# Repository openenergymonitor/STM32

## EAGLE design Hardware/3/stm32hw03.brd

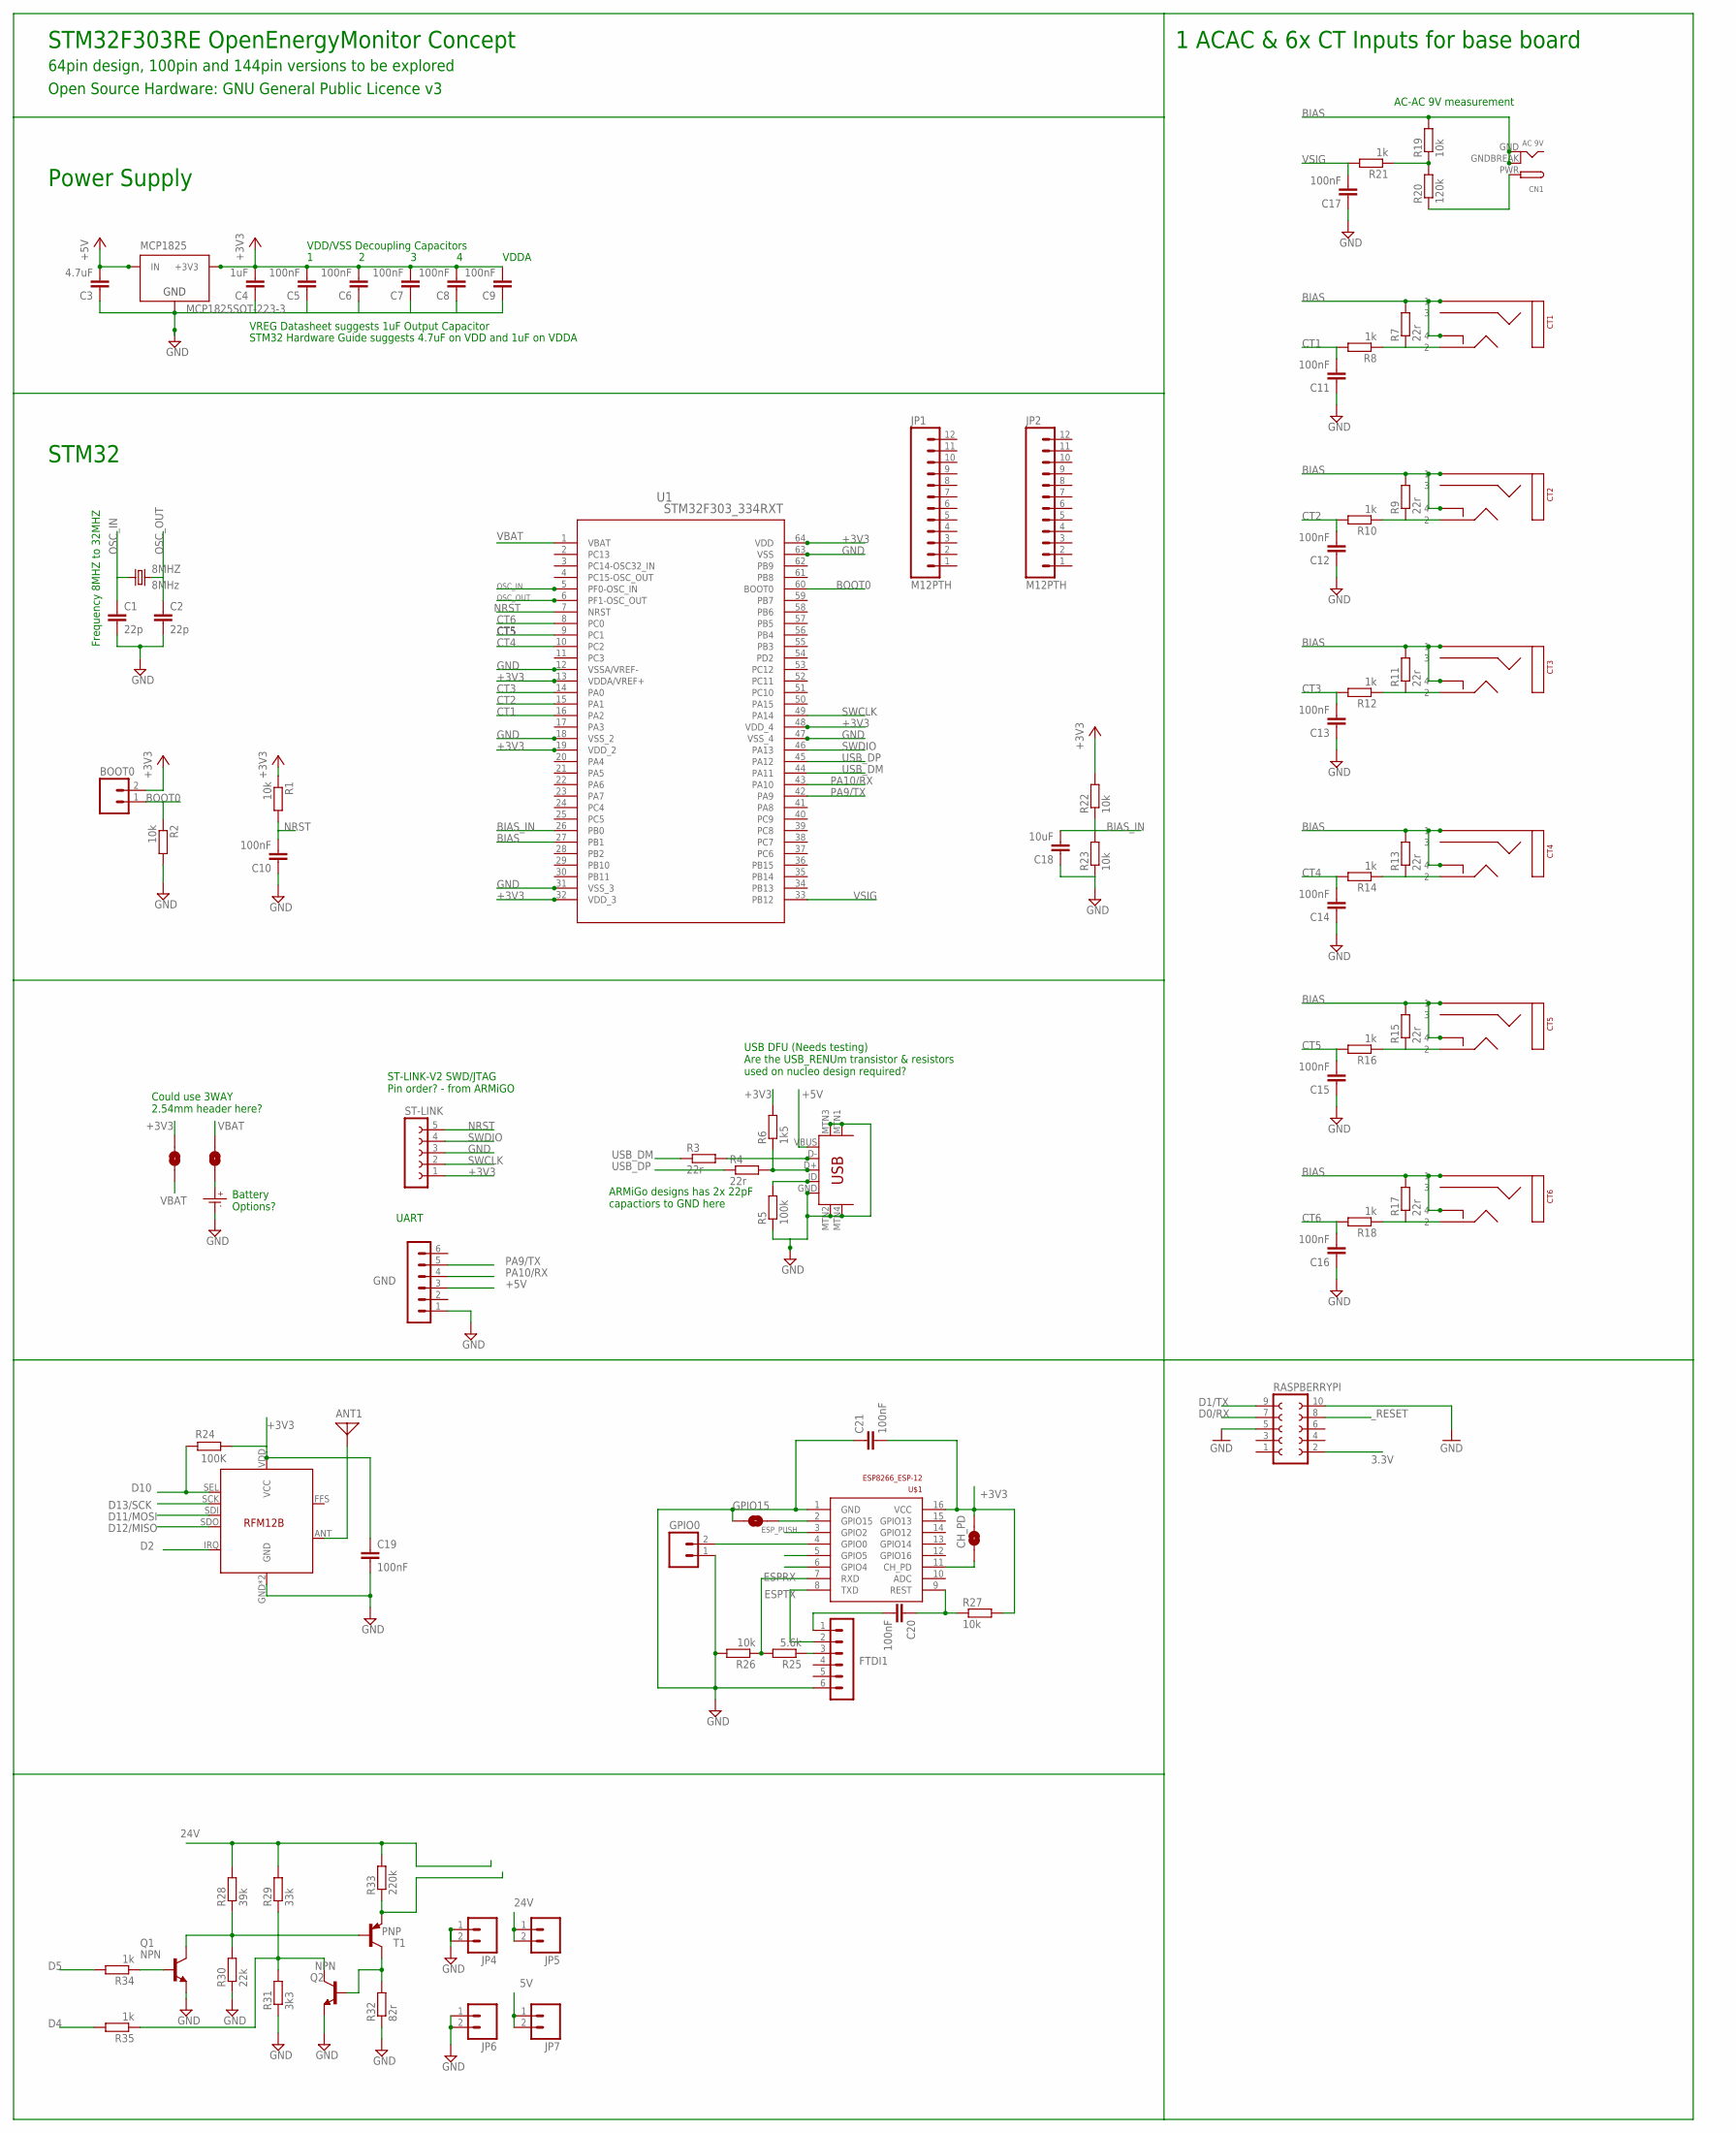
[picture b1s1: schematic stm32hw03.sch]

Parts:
3V3: SOLDERJUMPERNO; SJ_2S-NO
8MHZ: 8MHz; CRYSTAL-SMD-5X3
ANT1: ANTENNA; PAD-01
BATTERY: SOLDERJUMPERNO; SJ_2S-NO
BOOT0: M02PTH; 1X02
C1, C2: 22p; C0603
C3: 4.7uF; C0603
C4: 1uF; C0603
C5, C6, C7, C8, C9, C10, C11, C12, C13, C14, C15, C16, C17, C19, C20, C21: 100nF; C0603
C18: 10uF; C0603
CH_PD: SOLDERJUMPERNO; SJ_2S-NO
CN1: AC 9V; DCJACK_2MM_PTH
CR1220: CR1220SMD; MPN Harwin S8411-45R
CT1, CT2, CT3, CT4, CT5, CT6: STEREO_SMD; STEREO_SMT
FTDI1: FTDI; MA06-1
GND: UART; MA06-1
GPIO0: M02PTH; 1X02
GPIO15: SOLDERJUMPERNO; SJ_2S-NO
JP1, JP2: M12PTH; 1X12
JP4, JP5, JP6, JP7: M02PTH; 1X02
MCP1825: MCP1825SOT-223-3; SOT-223
Q1, Q2: NPN; SOT23-BEC
R1, R2, R19, R22, R23, R26, R27: 10k; R0603
R3, R4, R7, R9, R11, R13, R15, R17: 22r; R0603
R5: 100k; R0603
R6: 1k5; R0603
R8, R10, R12, R14, R16, R18, R21, R34, R35: 1k; R0603
R20: 120k; R0603
R24: 100K; R0603
R25: 5.6k; R0603
R28: 39k; R0603
R29: 33k; R0603
R30: 22k; R0603
R31: 3k3; R0603
R32: 82r; R0603
R33: 220k; R0603
RASPBERRYPI: FE05-2
ST-LINK: FE05-1
T1: PNP; SOT23
U1: STM32F303_334RXT; LQFP64-10X10MM
U$1: ESP8266_ESP-12; ESP8266-ESP12
U$10: USB-MINIB-5PIN; USB-MINIB-CISECO
U$14: RFM12B

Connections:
3.3V: RASPBERRYPI.2
5V: JP7.1, JP7.2
24V: JP5.1, JP5.2, R28.2, R29.2, R33.2
+3V3: 3V3.1, BOOT0.2, C4.2, C5.2, C6.2, C7.2, C8.2, C9.2, C19.1, C21.2, CH_PD.1, MCP1825.3 (+3V3), R1.1, R6.2, R22.2, R24.1, R27.2, ST-LINK.1, U1.13 (VDDA/VREF+), U1.19 (VDD_2), U1.32 (VDD_3), U1.48 (VDD_4), U1.64 (VDD), U$1.16 (VCC), U$14.VDD (VCC); also elsewhere on the board
+5V: C3.2, GND.3, MCP1825.1 (IN), U$10.VBUS
AC: CN1.PWR, R20.1
ADC0: R19.1, R20.2, R21.1
BIAS: CN1.GND, CN1.GNDBREAK, CT1.P$1 (1), CT1.P$4 (4), CT2.P$1 (1), CT2.P$4 (4), CT3.P$1 (1), CT3.P$4 (4), CT4.P$1 (1), CT4.P$4 (4), CT5.P$1 (1), CT5.P$4 (4), CT6.P$1 (1), CT6.P$4 (4), R7.2, R9.2, R11.2, R13.2, R15.2, R17.2, R19.2, U1.27 (PB1)
BIAS_IN: C18.2, R22.1, R23.2, U1.26 (PB0)
BOOT0: BOOT0.1, R2.1, U1.60 (BOOT0)
CT1: C11.2, R8.2, U1.16 (PA2)
CT2: C12.2, R10.2, U1.15 (PA1)
CT3: C13.2, R12.2, U1.14 (PA0)
CT4: C14.2, R14.2, U1.10 (PC2)
CT5: C15.2, R16.2, U1.9 (PC1)
CT6: C16.2, R18.2, U1.8 (PC0)
D0/RX: RASPBERRYPI.7
D1/TX: RASPBERRYPI.9
D2: U$14.IRQ
D4: R35.2
D5: R34.2
D10: R24.2, U$14.SEL
D11/MOSI: U$14.SDI
D12/MISO: U$14.SDO
D13/SCK: U$14.SCK
DIG1: ANT1.1, U$14.ANT
ESPRX: R25.2, R26.1, U$1.7 (RXD)
ESPTX: FTDI1.2, U$1.8 (TXD)
ESP_PUSH: U$1.3 (GPIO2)
GND: C1.2, C2.2, C3.1, C4.1, C5.1, C6.1, C7.1, C8.1, C9.1, C10.1, C11.1, C12.1, C13.1, C14.1, C15.1, C16.1, C17.1, C18.1, C19.2, C21.1, CR1220.P- (P$-), FTDI1.6, GND.1, GPIO0.1, GPIO15.2, JP4.1, JP4.2, JP6.1, JP6.2, MCP1825.2 (GND), Q1.E, Q2.E, R2.2, R5.1, R23.1, R26.2, R30.1, R31.1, R32.1, RASPBERRYPI.5, RASPBERRYPI.10, ST-LINK.3, U1.12 (VSSA/VREF-), U1.18 (VSS_2), U1.31 (VSS_3), U1.47 (VSS_4), U1.63 (VSS), U$1.1 (GND), U$10.GND, U$10.MTN1 (MTN2), U$10.MTN2 (MTN3), U$10.MTN3 (MTN1), U$10.MTN4, U$14.GND, U$14.P$12 (GND); also elsewhere on the board
unnamed: BATTERY.2, CR1220.P+ (P$+)
unnamed: CT1.P$2 (2), R7.1, R8.1
unnamed: R5.2, U$10.ID
unnamed: R4.2, R6.1, U$10.D+
unnamed: R3.2, U$10.D-
unnamed: CT2.P$2 (2), R9.1, R10.1
unnamed: C20.2, FTDI1.1
unnamed: CT3.P$2 (2), R11.1, R12.1
unnamed: CT4.P$2 (2), R13.1, R14.1
unnamed: R33.1, T1.2 (E)
unnamed: CT5.P$2 (2), R15.1, R16.1
unnamed: Q2.B, R32.2, T1.3 (C)
unnamed: CT6.P$2 (2), R17.1, R18.1
unnamed: Q1.C, R28.1, R30.2, T1.1 (B)
unnamed: Q2.C, R29.1, R31.2, R35.1
unnamed: Q1.B, R34.1
unnamed: GPIO15.1, U$1.2 (GPIO15)
unnamed: GPIO0.2, U$1.4 (GPIO0)
unnamed: FTDI1.3, R25.1
unnamed: CH_PD.2, U$1.11 (CH_PD)
unnamed: C20.1, R27.1, U$1.9 (REST)
NRST: C10.2, R1.2, ST-LINK.5, U1.7 (NRST)
OSC_IN: 8MHZ.1, C1.1, U1.5 (PF0-OSC_IN)
OSC_OUT: 8MHZ.3 (2), C2.1, U1.6 (PF1-OSC_OUT)
PA9/TX: GND.5, U1.42 (PA9)
PA10/RX: GND.4, U1.43 (PA10)
SWCLK: ST-LINK.2, U1.49 (PA14)
SWDIO: ST-LINK.4, U1.46 (PA13)
USB_DM: R3.1, U1.44 (PA11)
USB_DP: R4.1, U1.45 (PA12)
VBAT: 3V3.2, BATTERY.1, U1.1 (VBAT)
VSIG: C17.2, R21.2, U1.33 (PB12)
_RESET: RASPBERRYPI.8

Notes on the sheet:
VDD/VSS Decoupling Capacitors
VDDA
VREG Datasheet suggests 1uF Output Capacitor
STM32 Hardware Guide suggests 4.7uF on VDD and 1uF on VDDA
Frequency 8MHZ to 32MHZ
Could use 3WAY 2.54mm header here?
Battery Options?
ST-LINK-V2 SWD/JTAG Pin order? - from ARMiGO
UART
USB DFU (Needs testing) Are the USB_RENUm transistor & resistors used on nucleo design required?
ARMiGo designs has 2x 22pF capactiors to GND here
AC-AC 9V measurement
1 ACAC & 6x CT Inputs for base board
STM32F303RE OpenEnergyMonitor Concept
64pin design, 100pin and 144pin versions to be explored
Power Supply
STM32
Open Source Hardware: GNU General Public Licence v3

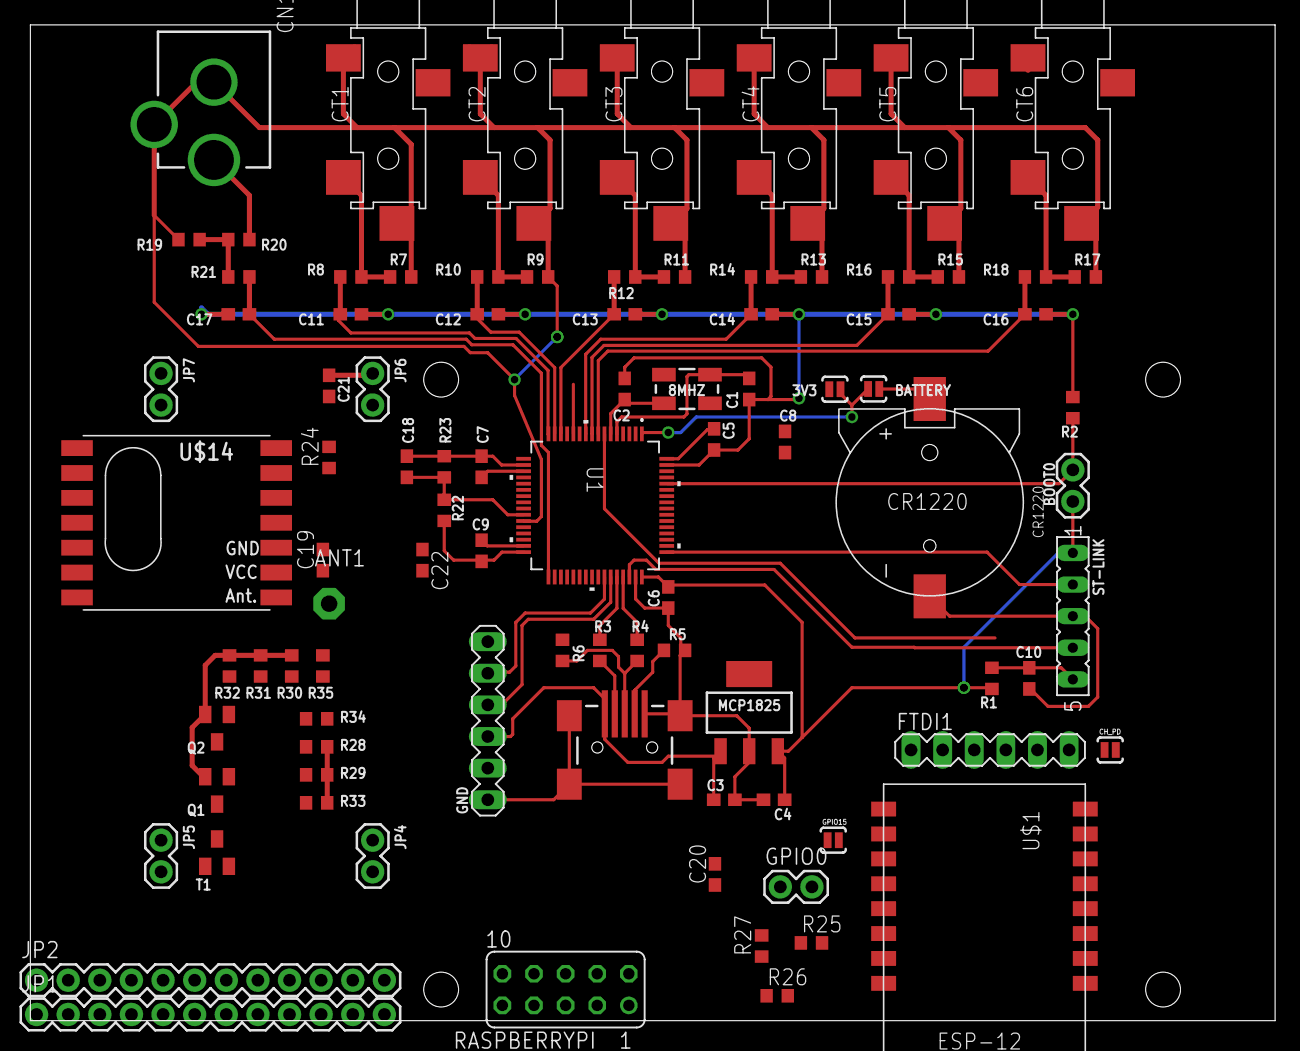
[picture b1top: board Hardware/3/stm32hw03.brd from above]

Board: 2 copper layers, 100.0 x 80.0 mm, 91 parts (0 on the bottom side), 52 nets.

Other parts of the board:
C22: 1uF; C0603

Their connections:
+3V3: C22.2; also elsewhere on the board
GND: C22.1; also elsewhere on the board

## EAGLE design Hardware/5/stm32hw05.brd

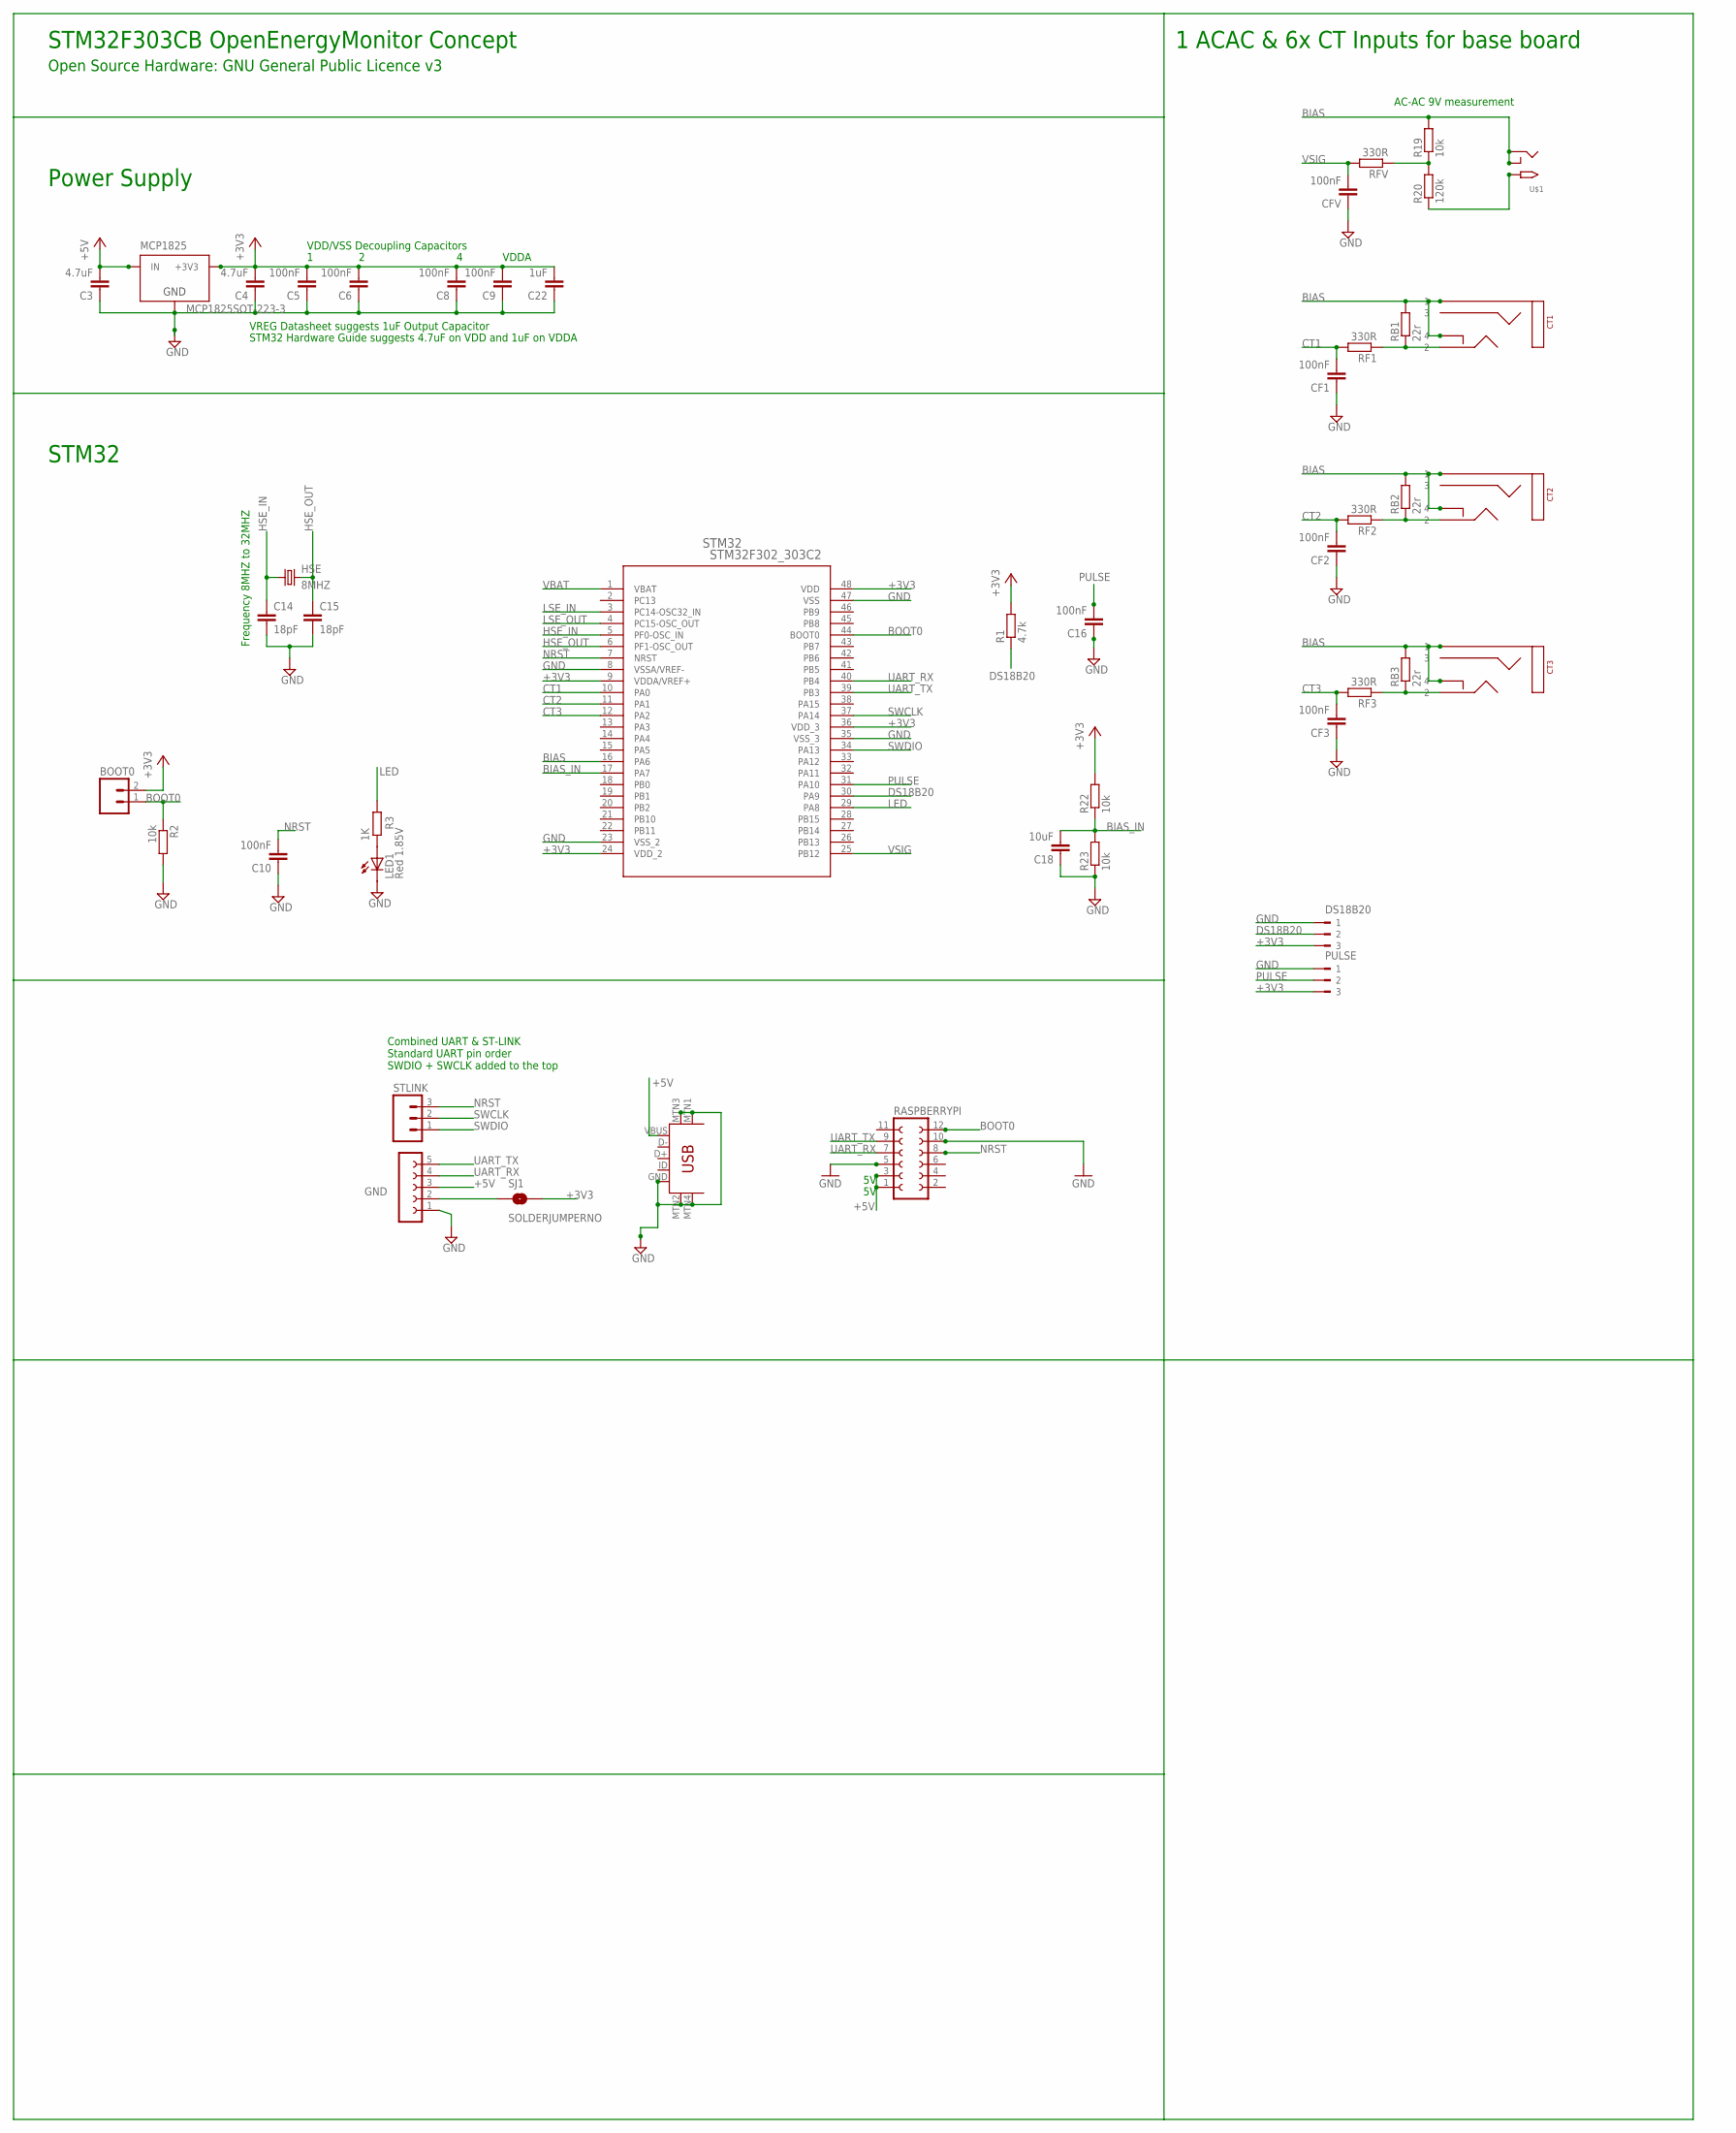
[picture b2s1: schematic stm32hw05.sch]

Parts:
BOOT0: M02PTH; 1X02
C3, C4: 4.7uF; C0603
C5, C6, C8, C9, C10, C16: 100nF; C0603
C14, C15: 18pF; C0603
C18: 10uF; C0603
C22: 1uF; C0603
CF1, CF2, CF3: 100nF; C0603
CFV: 100nF; C0603
CT1, CT2, CT3: STEREO_SMD; STEREO_SMT
DS18B20: 180-3
GND: UART; FE05-1
HSE: 8MHZ; CTS406
LED1: Red 1.85V; CHIP-LED0805
MCP1825: MCP1825SOT-223-3; SOT-223
PULSE: 180-3
R1: 4.7k; R0603
R2, R19, R22, R23: 10k; R0603
R3: 1K; R0603
R20: 120k; R0603
RASPBERRYPI: FE06-2
RB1, RB2, RB3: 22r; R0603
RF1, RF2, RF3: 330R; R0603
RFV: 330R; R0603
SJ1: SOLDERJUMPERNO; SJ_2S-NO
STLINK: M03PTH; 1X03
STM32: STM32F302_303C2; LQFP48-7X7MM
U$1: 2.1MMJACKSMT; DCJACK_2MM_SMT
U$10: USB-MINIB-5PIN; USB-MINIB-CISECO

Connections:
+3V3: BOOT0.2, C4.2, C5.2, C6.2, C8.2, C9.2, C22.2, DS18B20.3, MCP1825.3 (+3V3), PULSE.3, R1.2, R22.2, SJ1.2, STM32.9 (VDDA/VREF+), STM32.24 (VDD_2), STM32.36 (VDD_3), STM32.48 (VDD)
+5V: C3.2, GND.3, MCP1825.1 (IN), RASPBERRYPI.1, RASPBERRYPI.3, U$10.VBUS
AC: R20.1, U$1.PWR2 (TIP)
ADC0: R19.1, R20.2, RFV.1
BIAS: CT1.P$1 (1), CT1.P$4 (4), CT2.P$1 (1), CT2.P$4 (4), CT3.P$1 (1), CT3.P$4 (4), R19.2, RB1.2, RB2.2, RB3.2, STM32.16 (PA6), U$1.GND (RING), U$1.GNDBREAK (RING_SW)
BIAS_IN: C18.2, R22.1, R23.2, STM32.17 (PA7)
BOOT0: BOOT0.1, R2.1, RASPBERRYPI.12, STM32.44 (BOOT0)
CT1: CF1.2, RF1.2, STM32.10 (PA0)
CT2: CF2.2, RF2.2, STM32.11 (PA1)
CT3: CF3.2, RF3.2, STM32.12 (PA2)
DS18B20: DS18B20.2, R1.1, STM32.30 (PA9)
GND: C3.1, C4.1, C5.1, C6.1, C8.1, C9.1, C10.1, C14.2, C15.2, C16.1, C18.1, C22.1, CF1.1, CF2.1, CF3.1, CFV.1, DS18B20.1, GND.1, LED1.C, MCP1825.2 (GND), PULSE.1, R2.2, R23.1, RASPBERRYPI.5, RASPBERRYPI.10, STM32.8 (VSSA/VREF-), STM32.23 (VSS_2), STM32.35 (VSS_3), STM32.47 (VSS), U$10.GND, U$10.MTN1 (MTN2), U$10.MTN2 (MTN3), U$10.MTN3 (MTN1), U$10.MTN4
HSE_IN: C14.1, HSE.1, STM32.5 (PF0-OSC_IN)
HSE_OUT: C15.1, HSE.3 (2), STM32.6 (PF1-OSC_OUT)
LED: R3.2, STM32.29 (PA8)
LSE_IN: STM32.3 (PC14-OSC32_IN)
LSE_OUT: STM32.4 (PC15-OSC_OUT)
unnamed: GND.2, SJ1.1
unnamed: CT1.P$2 (2), RB1.1, RF1.1
unnamed: CT2.P$2 (2), RB2.1, RF2.1
unnamed: CT3.P$2 (2), RB3.1, RF3.1
unnamed: LED1.A, R3.1
NRST: C10.2, RASPBERRYPI.8, STLINK.3, STM32.7 (NRST)
PULSE: C16.2, PULSE.2, STM32.31 (PA10)
SWCLK: STLINK.2, STM32.37 (PA14)
SWDIO: STLINK.1, STM32.34 (PA13)
UART_RX: GND.4, RASPBERRYPI.7, STM32.40 (PB4)
UART_TX: GND.5, RASPBERRYPI.9, STM32.39 (PB3)
VBAT: STM32.1 (VBAT)
VSIG: CFV.2, RFV.2, STM32.25 (PB12)

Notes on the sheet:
VDD/VSS Decoupling Capacitors
VDDA
VREG Datasheet suggests 1uF Output Capacitor
STM32 Hardware Guide suggests 4.7uF on VDD and 1uF on VDDA
Combined UART & ST-LINK Standard UART pin order SWDIO + SWCLK added to the top
AC-AC 9V measurement
1 ACAC & 6x CT Inputs for base board
STM32F303CB OpenEnergyMonitor Concept
Power Supply
STM32
Open Source Hardware: GNU General Public Licence v3
Frequency 8MHZ to 32MHZ

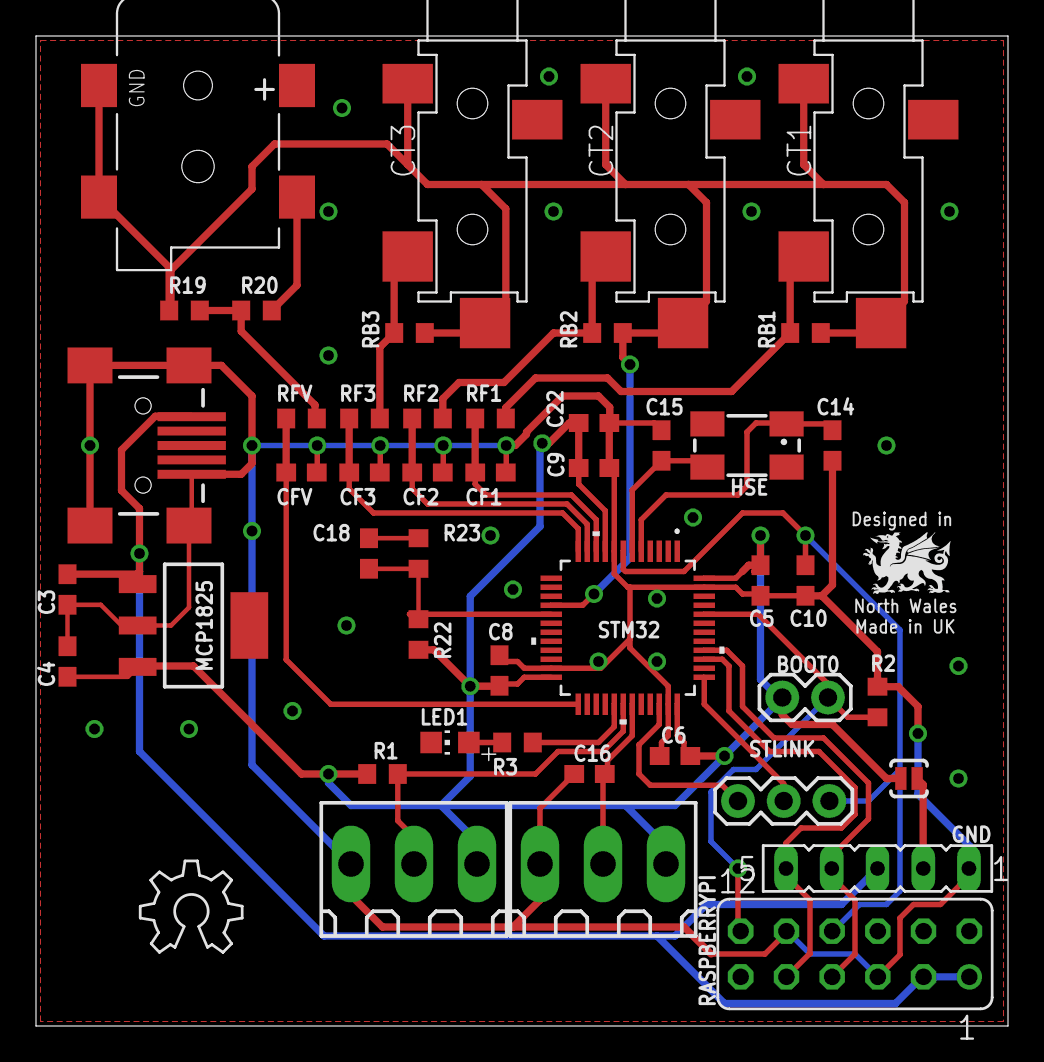
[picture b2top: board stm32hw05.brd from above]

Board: 2 copper layers, 54.0 x 55.0 mm, 47 parts (0 on the bottom side), 27 nets.

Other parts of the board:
LOGO1: OSHW_LOGO_6MILX0200-NT; OSHW_6X200_NOTEXT

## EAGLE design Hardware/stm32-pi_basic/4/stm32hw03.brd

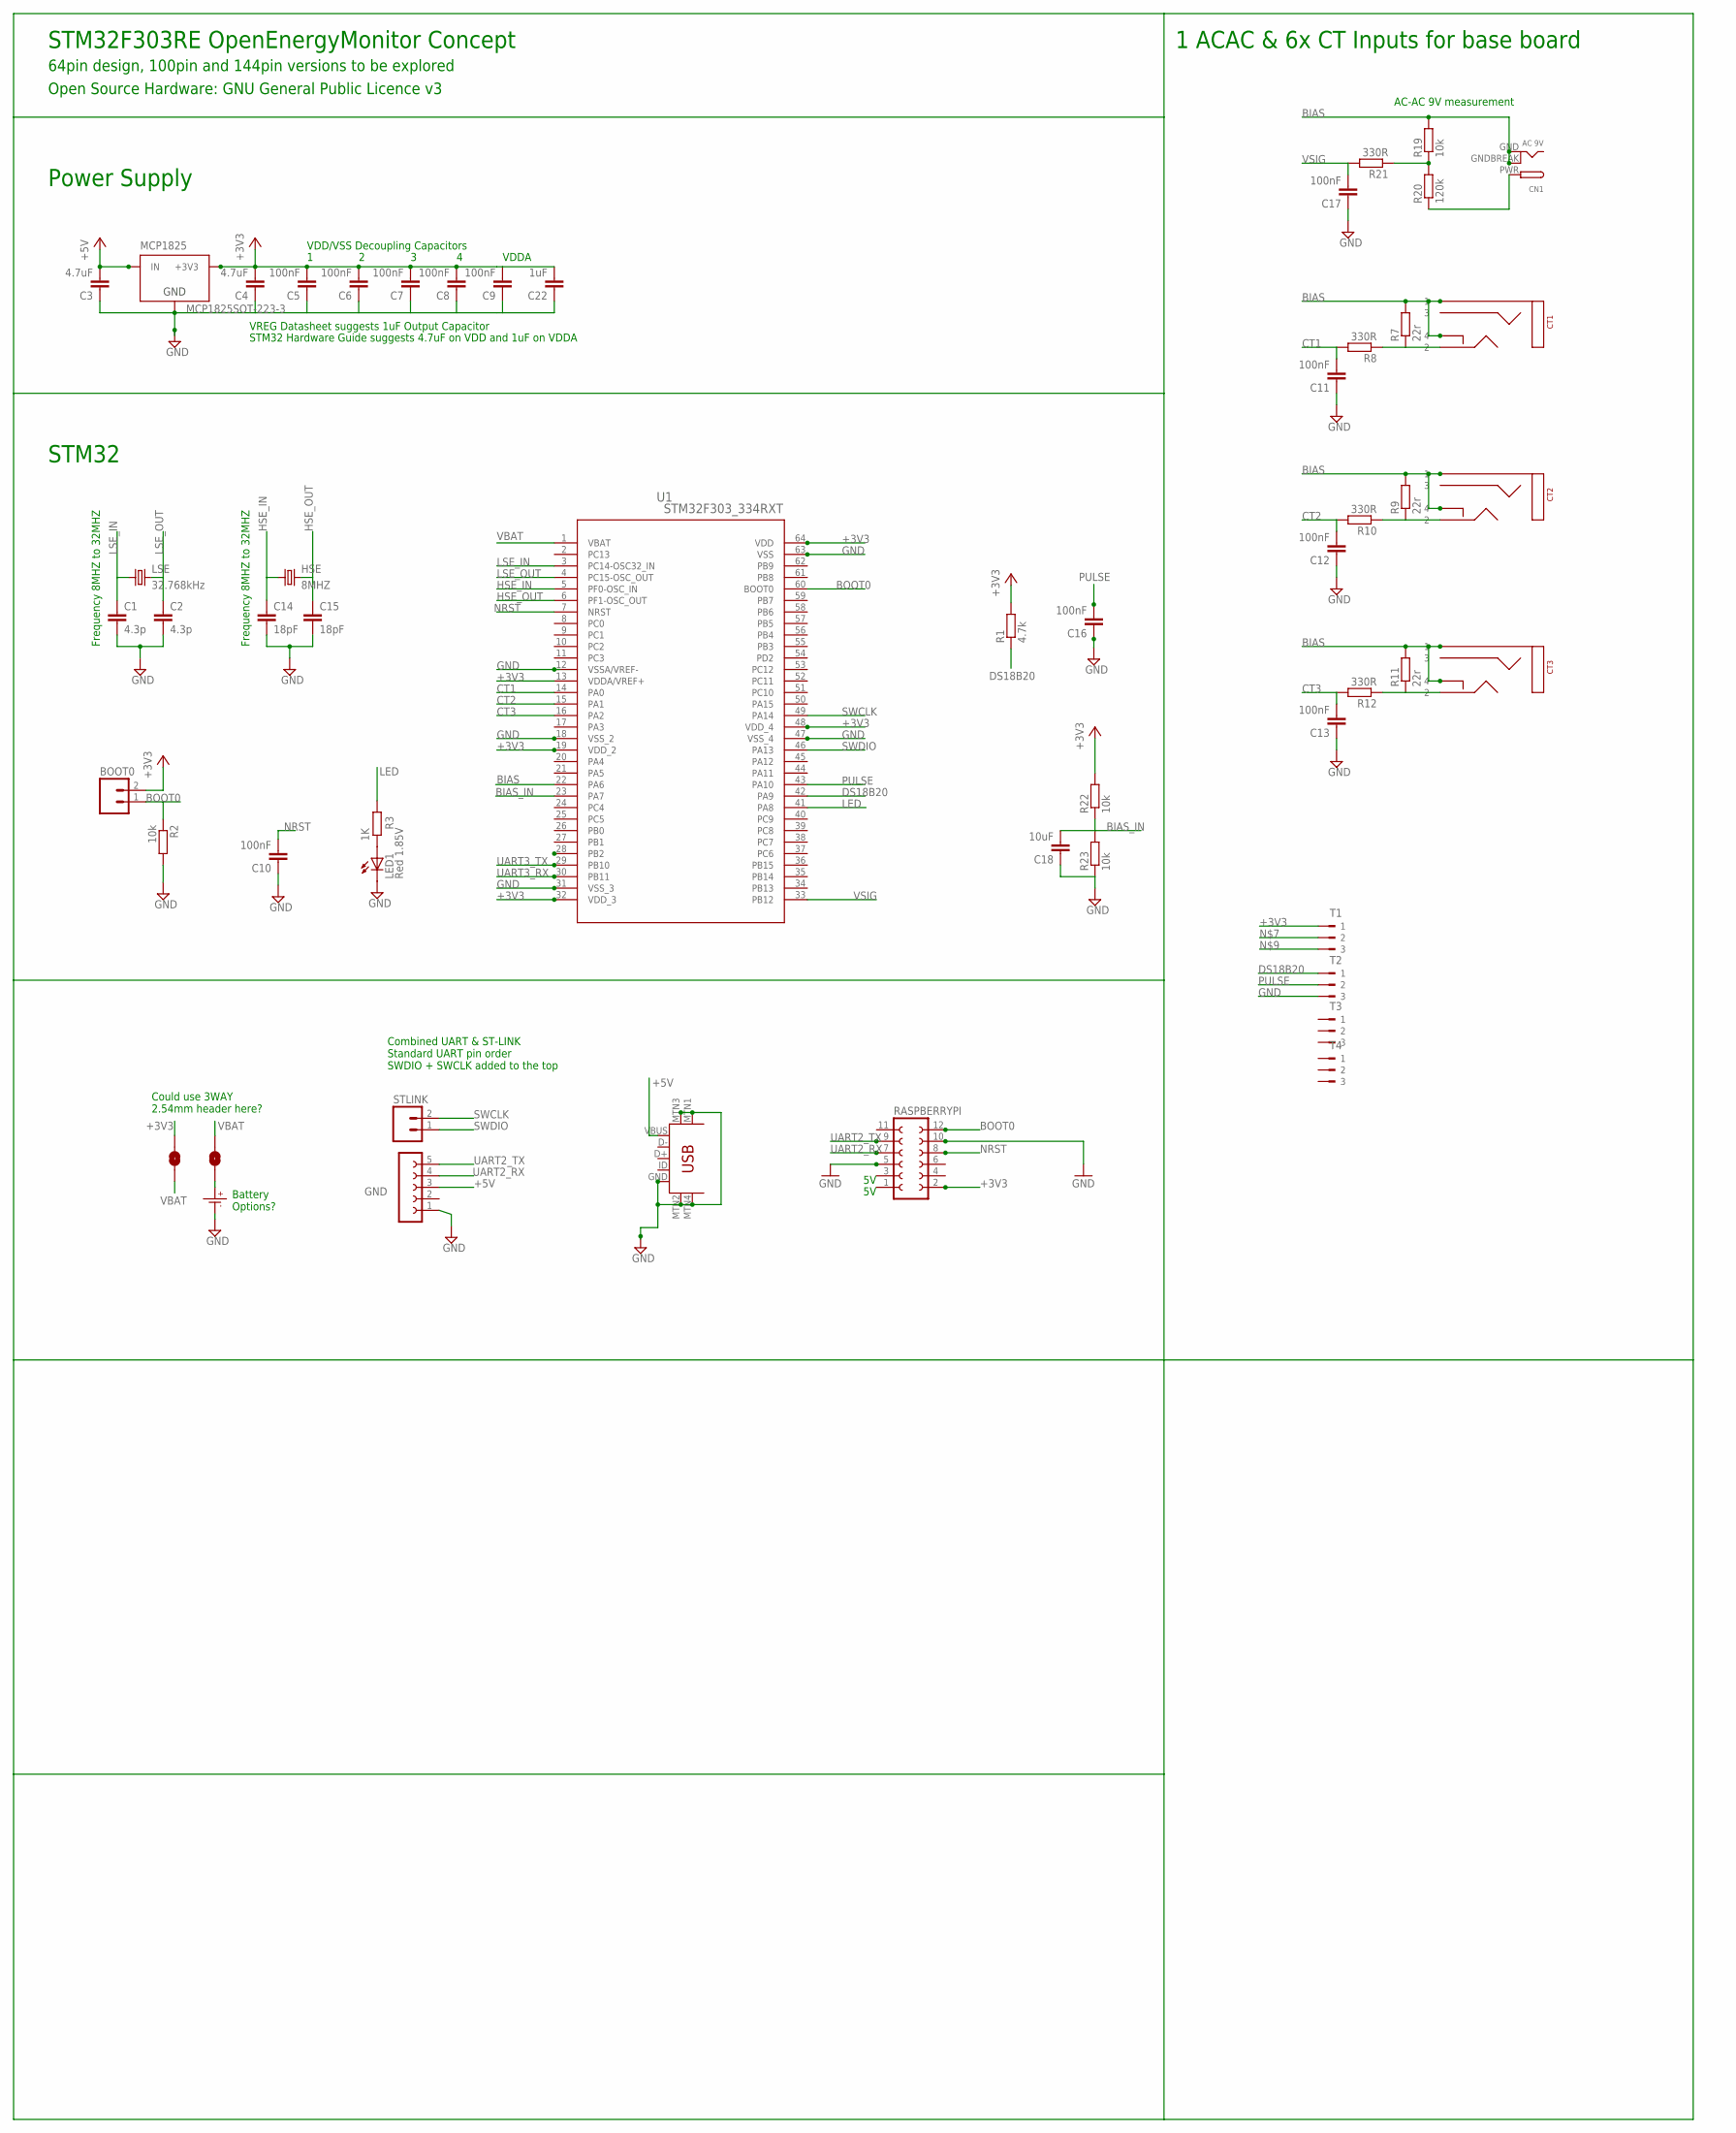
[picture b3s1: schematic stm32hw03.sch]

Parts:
3V3: SOLDERJUMPERNO; SJ_2S-NO
BATTERY: SOLDERJUMPERNO; SJ_2S-NO
BOOT0: M02PTH; 1X02
C1, C2: 4.3p; C0603
C3, C4: 4.7uF; C0603
C5, C6, C7, C8, C9, C10, C11, C12, C13, C16, C17: 100nF; C0603
C14, C15: 18pF; C0603
C18: 10uF; C0603
C22: 1uF; C0603
CN1: AC 9V; DCJACK_2MM_PTH
CR1220: CR1220SMD; MPN Harwin S8411-45R
CT1, CT2, CT3: STEREO_SMD; STEREO_SMT
GND: UART; FE05-1
HSE: 8MHZ; CTS406
LED1: Red 1.85V; CHIP-LED0805
LSE: 32.768kHz; MC-306
MCP1825: MCP1825SOT-223-3; SOT-223
R1: 4.7k; R0603
R2, R19, R22, R23: 10k; R0603
R3: 1K; R0603
R7, R9, R11: 22r; R0603
R8, R10, R12, R21: 330R; R0603
R20: 120k; R0603
RASPBERRYPI: FE06-2
STLINK: M02PTH; 1X02
T1, T2, T3, T4: 180-3
U1: STM32F303_334RXT; LQFP64-10X10MM
U$10: USB-MINIB-5PIN; USB-MINIB-CISECO

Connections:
+3V3: 3V3.1, BOOT0.2, C4.2, C5.2, C6.2, C7.2, C8.2, C9.2, C22.2, MCP1825.3 (+3V3), R1.2, R22.2, RASPBERRYPI.2, T1.1, U1.13 (VDDA/VREF+), U1.19 (VDD_2), U1.32 (VDD_3), U1.48 (VDD_4), U1.64 (VDD)
+5V: C3.2, GND.3, MCP1825.1 (IN), U$10.VBUS
AC: CN1.PWR, R20.1
ADC0: R19.1, R20.2, R21.1
BIAS: CN1.GND, CN1.GNDBREAK, CT1.P$1 (1), CT1.P$4 (4), CT2.P$1 (1), CT2.P$4 (4), CT3.P$1 (1), CT3.P$4 (4), R7.2, R9.2, R11.2, R19.2, U1.22 (PA6)
BIAS_IN: C18.2, R22.1, R23.2, U1.23 (PA7)
BOOT0: BOOT0.1, R2.1, RASPBERRYPI.12, U1.60 (BOOT0)
CT1: C11.2, R8.2, U1.14 (PA0)
CT2: C12.2, R10.2, U1.15 (PA1)
CT3: C13.2, R12.2, U1.16 (PA2)
DS18B20: R1.1, T2.1, U1.42 (PA9)
GND: C1.2, C2.2, C3.1, C4.1, C5.1, C6.1, C7.1, C8.1, C9.1, C10.1, C11.1, C12.1, C13.1, C14.2, C15.2, C16.1, C17.1, C18.1, C22.1, CR1220.P- (P$-), GND.1, LED1.C, MCP1825.2 (GND), R2.2, R23.1, RASPBERRYPI.5, RASPBERRYPI.10, T2.3, U1.12 (VSSA/VREF-), U1.18 (VSS_2), U1.31 (VSS_3), U1.47 (VSS_4), U1.63 (VSS), U$10.GND, U$10.MTN1 (MTN2), U$10.MTN2 (MTN3), U$10.MTN3 (MTN1), U$10.MTN4
HSE_IN: C14.1, HSE.1, U1.5 (PF0-OSC_IN)
HSE_OUT: C15.1, HSE.3 (2), U1.6 (PF1-OSC_OUT)
LED: R3.2, U1.41 (PA8)
LSE_IN: C1.1, LSE.1, U1.3 (PC14-OSC32_IN)
LSE_OUT: C2.1, LSE.4 (2), U1.4 (PC15-OSC_OUT)
unnamed: BATTERY.2, CR1220.P+ (P$+)
unnamed: CT1.P$2 (2), R7.1, R8.1
unnamed: CT2.P$2 (2), R9.1, R10.1
unnamed: CT3.P$2 (2), R11.1, R12.1
unnamed: LED1.A, R3.1
NRST: C10.2, RASPBERRYPI.8, U1.7 (NRST)
PULSE: C16.2, T2.2, U1.43 (PA10)
SWCLK: STLINK.2, U1.49 (PA14)
SWDIO: STLINK.1, U1.46 (PA13)
UART2_RX: GND.4, RASPBERRYPI.7
UART2_TX: GND.5, RASPBERRYPI.9
UART3_RX: U1.30 (PB11)
UART3_TX: U1.29 (PB10)
VBAT: 3V3.2, BATTERY.1, U1.1 (VBAT)
VSIG: C17.2, R21.2, U1.33 (PB12)

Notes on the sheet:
VDD/VSS Decoupling Capacitors
VDDA
VREG Datasheet suggests 1uF Output Capacitor
STM32 Hardware Guide suggests 4.7uF on VDD and 1uF on VDDA
Frequency 8MHZ to 32MHZ
Could use 3WAY 2.54mm header here?
Battery Options?
Combined UART & ST-LINK Standard UART pin order SWDIO + SWCLK added to the top
AC-AC 9V measurement
1 ACAC & 6x CT Inputs for base board
STM32F303RE OpenEnergyMonitor Concept
64pin design, 100pin and 144pin versions to be explored
Power Supply
STM32
Open Source Hardware: GNU General Public Licence v3

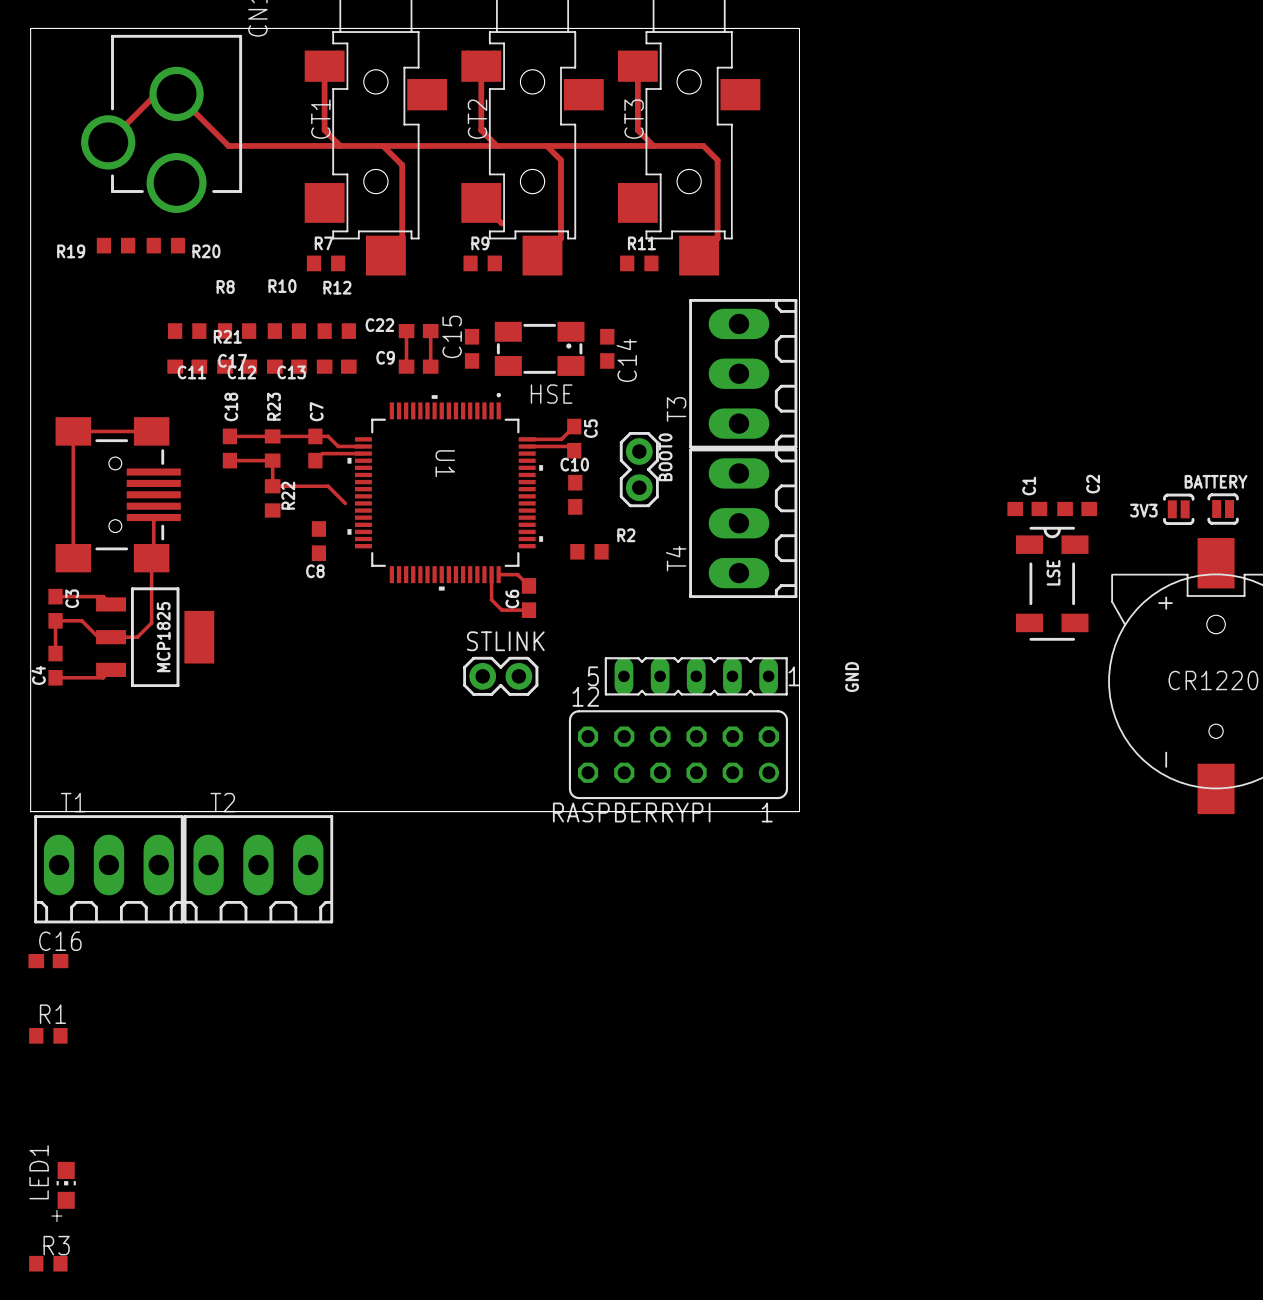
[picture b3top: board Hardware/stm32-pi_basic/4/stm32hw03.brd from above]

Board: 2 copper layers, 54.0 x 55.0 mm, 54 parts (0 on the bottom side), 30 nets.
